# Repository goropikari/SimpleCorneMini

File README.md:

# simple corne mini

simple corne mini is modified version of [corne cherry v2](https://github.com/foostan/crkbd/releases/tag/corne-cherry-v2.1.0).

pcb data is made by KiCad 6.

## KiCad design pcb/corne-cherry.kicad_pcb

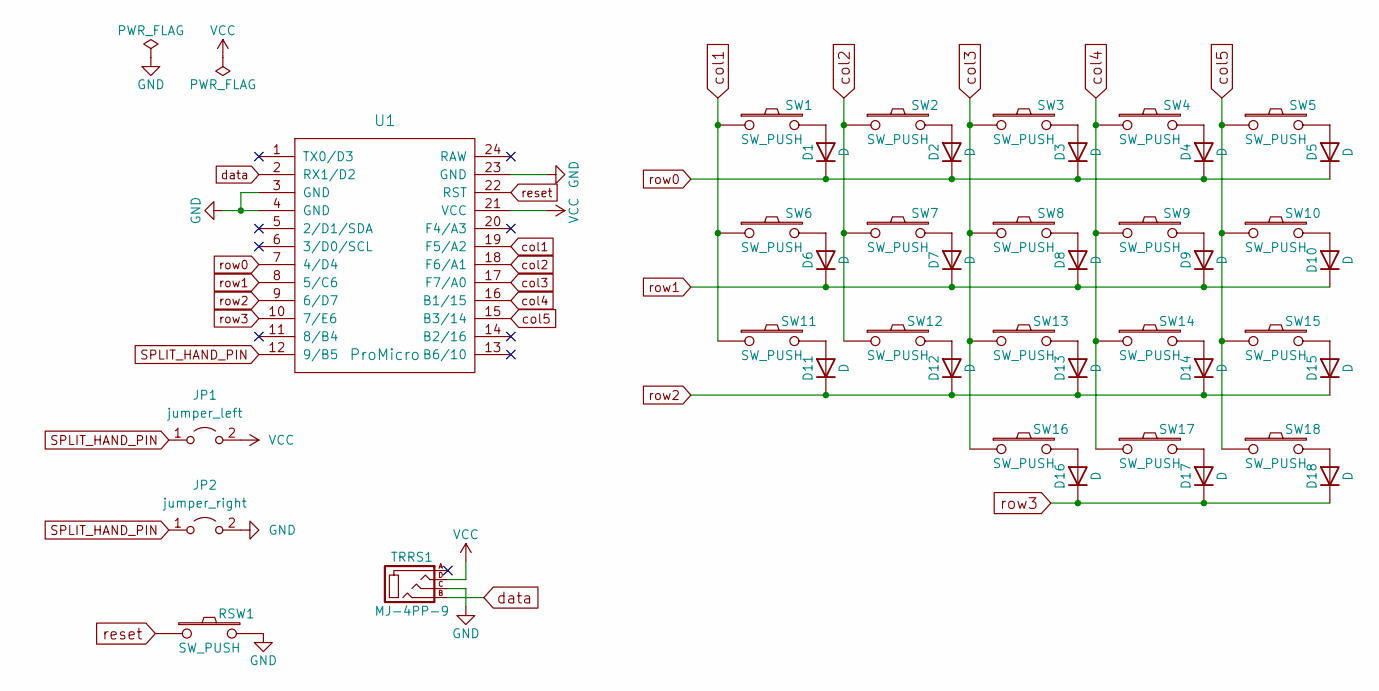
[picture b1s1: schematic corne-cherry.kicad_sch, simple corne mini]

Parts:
D1, D2, D3, D4, D5, D6, D7, D8, D9, D10, D11, D12, D13, D14, D15, D16, D17, D18: D; D3_SMD
JP1: jumper_left; SolderJumper-2_P1.3mm_Open_TrianglePad1.0x1.5mm
JP2: jumper_right; SolderJumper-2_P1.3mm_Open_TrianglePad1.0x1.5mm
RSW1: SW_PUSH; ResetSW
SW1, SW2, SW3, SW4, SW5, SW6, SW7, SW8, SW9, SW10, SW11, SW12, SW13, SW14, SW15, SW16, SW17, SW18: SW_PUSH; CherryMX_MidHeight_Hotswap
TRRS1: MJ-4PP-9
U1: ProMicro; ProMicro_reversible

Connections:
GND: JP2.2 (B), RSW1.2, TRRS1.C, U1.3 (GND), U1.4 (GND), U1.23 (GND)
unnamed: D1.2 (A), SW1.2
unnamed: D2.2 (A), SW2.2
unnamed: D3.2 (A), SW3.2
unnamed: D4.2 (A), SW4.2
unnamed: D5.2 (A), SW5.2
unnamed: D6.2 (A), SW6.2
unnamed: D7.2 (A), SW7.2
unnamed: D8.2 (A), SW8.2
unnamed: D9.2 (A), SW9.2
unnamed: D10.2 (A), SW10.2
unnamed: D11.2 (A), SW11.2
unnamed: D12.2 (A), SW12.2
unnamed: D13.2 (A), SW13.2
unnamed: D14.2 (A), SW14.2
unnamed: D15.2 (A), SW15.2
unnamed: D16.2 (A), SW16.2
unnamed: D17.2 (A), SW17.2
unnamed: D18.2 (A), SW18.2
SPLIT_HAND_PIN: JP1.1 (A), JP2.1 (A), U1.12 (9/B5)
VCC: JP1.2 (B), TRRS1.D, U1.21 (VCC)
col1: SW1.1, SW6.1, SW11.1, U1.19 (F5/A2)
col2: SW2.1, SW7.1, SW12.1, U1.18 (F6/A1)
col3: SW3.1, SW8.1, SW13.1, SW16.1, U1.17 (F7/A0)
col4: SW4.1, SW9.1, SW14.1, SW17.1, U1.16 (B1/15)
col5: SW5.1, SW10.1, SW15.1, SW18.1, U1.15 (B3/14)
data: TRRS1.B, U1.2 (RX1/D2)
reset: RSW1.1, U1.22 (RST)
row0: D1.1 (K), D2.1 (K), D3.1 (K), D4.1 (K), D5.1 (K), U1.7 (4/D4)
row1: D6.1 (K), D7.1 (K), D8.1 (K), D9.1 (K), D10.1 (K), U1.8 (5/C6)
row2: D11.1 (K), D12.1 (K), D13.1 (K), D14.1 (K), D15.1 (K), U1.9 (6/D7)
row3: D16.1 (K), D17.1 (K), D18.1 (K), U1.10 (7/E6)

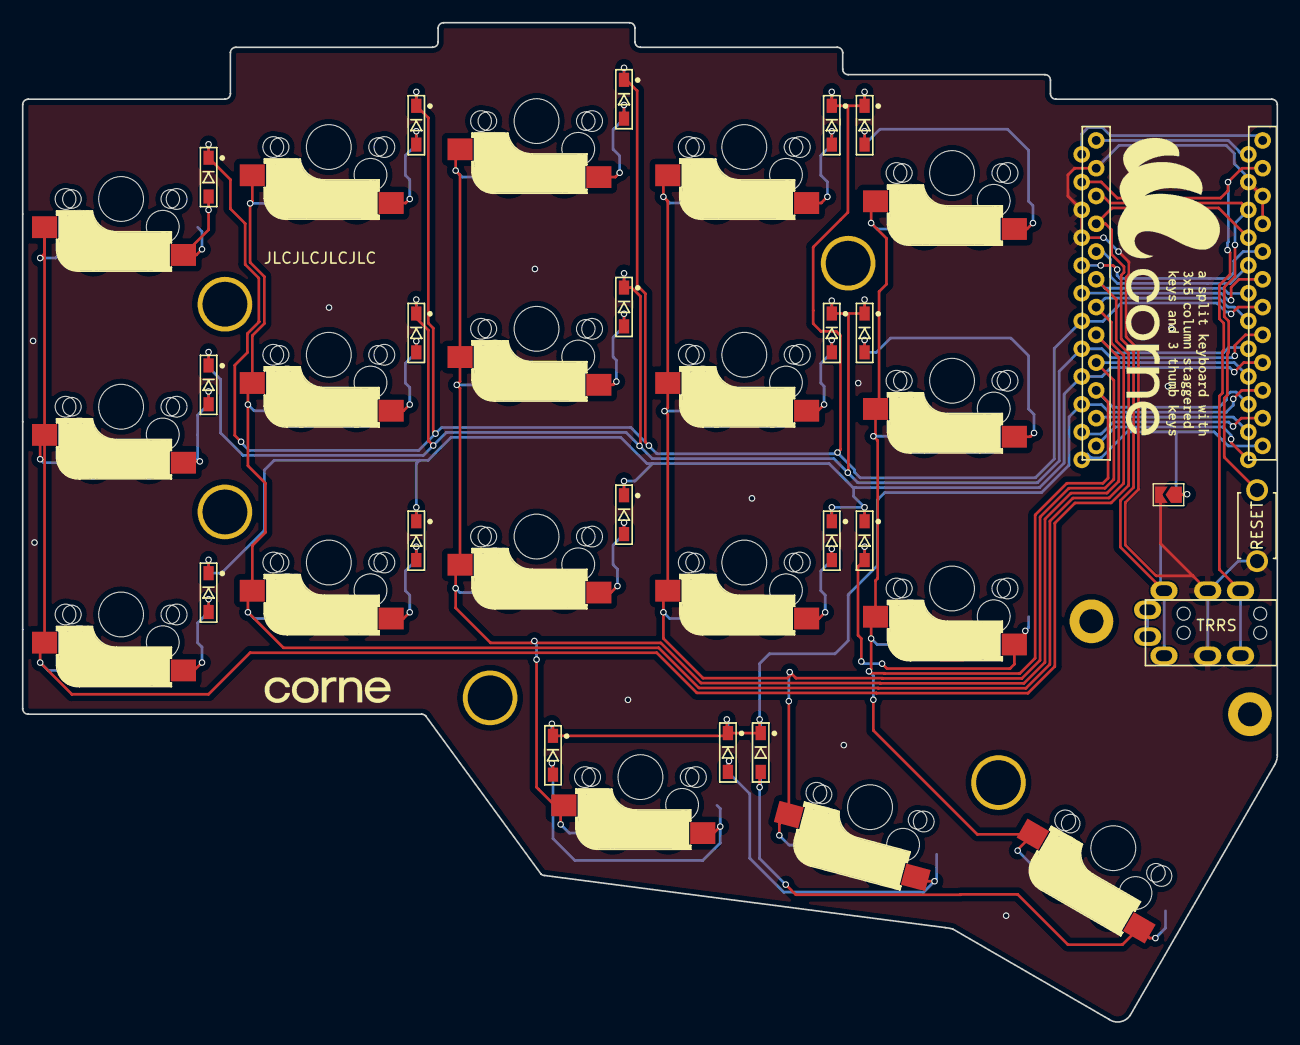
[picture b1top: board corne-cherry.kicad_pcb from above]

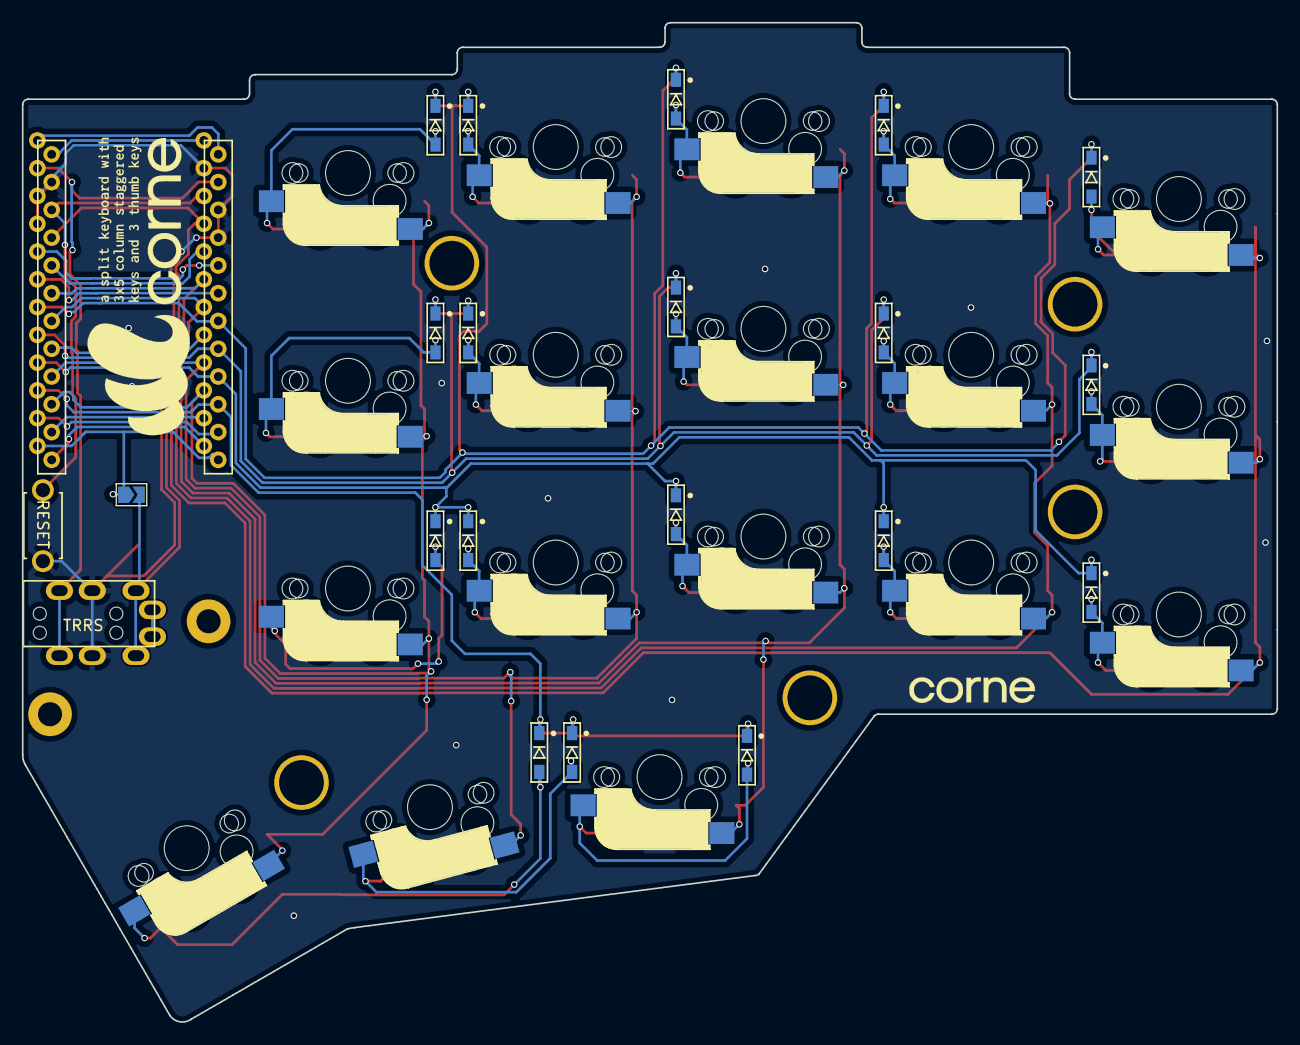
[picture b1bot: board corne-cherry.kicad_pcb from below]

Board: 2 copper layers, 114.8 x 91.4 mm, 50 parts (2 on the bottom side), 32 nets.

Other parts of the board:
G1, G2: LOGO; corne
H1, H2, H3, H4, H5: LEGO_HOLE
h1, h2: LEGO_HOLE

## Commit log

2023-02-16 Create LICENSE
2023-02-16 add pcb data
2023-02-16 add note
2023-02-26 add firmware
